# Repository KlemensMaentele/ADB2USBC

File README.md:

# ADB2USBC

**ADB-to-USB Converter for Apple Desktop Bus Keyboards**

ADB2USBC is a small PCB that allows vintage Apple ADB keyboards to be used as modern USB HID keyboards. The board is built around an ATmega32U2 microcontroller and is intended to run the ADB-to-USB converter firmware from the TMK Keyboard Firmware project.

## Overview

This project contains the hardware design files for an ADB-to-USB converter board.

Features:

* Supports Apple Desktop Bus (ADB) keyboards
* USB HID keyboard output
* ATmega32U2 microcontroller
* Compatible with TMK's ADB-to-USB converter firmware
* USB DFU bootloader support for firmware flashing

## Firmware

This repository does not include firmware.

The board is designed to run the ADB-to-USB converter implementation provided by the TMK Keyboard Firmware project:

TMK Keyboard Firmware:
https://github.com/tmk/tmk_keyboard

Please refer to the TMK documentation for building and flashing firmware.

## Hardware

The repository contains:

* KiCad project files
* Schematic
* Bill of Materials (BOM)
* Custom footprint, symbol and 3D model files for the ADB connector

### BOM

A Bill of Materials (BOM) is included for assembly. The provided BOM was created specifically for JLCPCB assembly services and includes the manufacturer part numbers used for the original build. Component availability may change over time, so substitutions may be required.

### Manufacturing

Gerber files are not included in this repository. They can be easily generated from the included KiCad project files using KiCad's built-in fabrication output tools.

### ISP Header

The board includes a standard 6-pin Atmel ISP header for development and debugging purposes.

For normal operation, the ISP header is not required. The ATmega32U2 can be programmed via its USB DFU bootloader, so the header may be removed.

## Pictures

### Assembled Board

### PCB

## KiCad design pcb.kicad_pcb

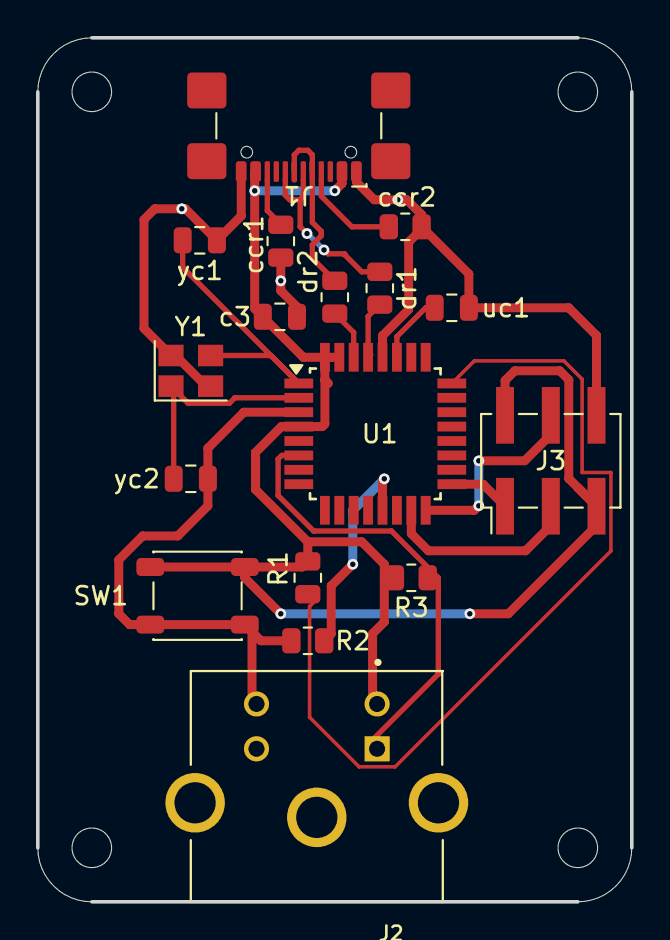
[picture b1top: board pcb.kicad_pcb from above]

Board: 2 copper layers, 33.0 x 48.0 mm, 21 parts (0 on the bottom side), 17 nets.

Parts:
H1, H2, H3, H4: MountingHole; MountingHole_2.2mm_M2
J1: USB4110-GF-A; USB_C_Receptacle_GCT_USB4110
J2: 5749181-1
J3: AVR-ISP-6; PinHeader_2x03_P2.54mm_Vertical_SMD
R1, R2: 10k; R_0805_2012Metric
R3: 1k; R_0805_2012Metric
SW1: SW_DPST_x2; SW_SPST_PTS647_Sx38
U1: ATmega32U2-A; TQFP-32_7x7mm_P0.8mm
Y1: Crystal_GND24; Crystal_SMD_Abracon_ABM8G-4Pin_3.2x2.5mm
c3: 10uf; C_0805_2012Metric
ccr1, ccr2: 5k1; R_0805_2012Metric
dr1, dr2: 22; R_0805_2012Metric
uc1: 1uf; C_0805_2012Metric
yc1, yc2: 26pf; C_0805_2012Metric

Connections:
GND: J1.A1 (GND_1), J1.A12 (GND), J1.B1 (GND), J1.B12 (GND), J2.4 (GND), J3.6 (GND), R2.2, SW1.1 (A), U1.3 (GND), U1.28 (UGND), Y1.2, Y1.4, c3.1, ccr1.2, ccr2.2, uc1.1, yc1.1, yc2.1
unnamed: J1.A5 (CC1), ccr2.1
unnamed: J1.B5 (CC2), ccr1.1
unnamed: J1.A7 (DN1), J1.B7 (Dn2), dr2.2
unnamed: J1.A6 (DP1), J1.B6 (DP2), dr1.2
unnamed: J1.A4 (VBus1), J1.A9 (VBus2), J1.B4 (VBUS3), J1.B9 (VBus4), J2.3 (VCC), J3.2 (VCC), J3.5 (~RST), R1.2, R3.2, SW1.2 (B), U1.4 (VCC), U1.31 (UVCC), U1.32 (AVCC), c3.2
unnamed: J2.1 (Data), R3.1, U1.6 (PD0)
unnamed: J3.1 (MISO), U1.17 (PB3)
unnamed: J3.4 (MOSI), U1.16 (PB2)
unnamed: J3.3 (SCK), U1.15 (PB1)
unnamed: U1.29 (D+), dr1.1
unnamed: U1.30 (D-), dr2.1
unnamed: U1.2 (PC0/XTAL2), Y1.1, yc2.2
unnamed: R1.1, U1.24 (PC1/~RESET)
unnamed: U1.27 (UCAP), uc1.2
unnamed: U1.1 (XTAL1), Y1.3, yc1.2
unnamed: R2.1, U1.13 (~HWB/PD7)

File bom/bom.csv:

Comment,Designator,Footprint,JLCPCB Part
10uf,c3,Capacitor_SMD:C_0805_2012Metric,
5k1,ccr1 ccr2,Resistor_SMD:R_0805_2012Metric,
22,dr1 dr2,Resistor_SMD:R_0805_2012Metric,
USB4110-GF-A,J1,Connector_USB:USB_C_Receptacle_GCT_USB4110,
5749181-1,J2,Library:57491811,
AVR-ISP-6,J3,Connector_PinHeader_2.54mm:PinHeader_2x03_P2.54mm_Vertical_SMD,
10k,R1 R2,Resistor_SMD:R_0805_2012Metric,
1k,R3,Resistor_SMD:R_0805_2012Metric,
SW_DPST_x2,SW1,Button_Switch_SMD:SW_SPST_PTS647_Sx38,
ATmega32U2-A,U1,Package_QFP:TQFP-32_7x7mm_P0.8mm,
1uf,uc1,Capacitor_SMD:C_0805_2012Metric,
Crystal_GND24,Y1,Crystal:Crystal_SMD_Abracon_ABM8G-4Pin_3.2x2.5mm,
26pf,yc1 yc2,Capacitor_SMD:C_0805_2012Metric,

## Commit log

2026-02-17 upload Files
2026-02-17 Restructure
2026-02-17 Upload pictures
2026-02-17 Restructure and add README
2026-06-16 Revise README for ADB2USBC project details
    Updated project description and features in README.md.
2026-06-16 Upload new picture
2026-06-16 change structure
2026-06-16 Fix pcb dcm errors
2026-06-16 Fix grammar and add notes in README
    Corrected grammar in the README and added notes about the ISP header and firmware flashing.
2026-06-16 Revise README for clarity on project components
    Updated README to clarify project files and BOM details.
2026-06-16 Change bom name
